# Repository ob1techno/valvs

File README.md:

# Vālvs
A cascading quad tube VCA module in Eurorack format (3U/32hp).

Vālvs provides four gnarly tube VCAs with drive, gain, feedback, and adjustable, switchable distortion controls.

Vālvs’ outputs are daisy-chained, allowing adjacent groups of 2, 3, or all 4 channels to be mixed together.

Based on/inspired by the work of [Ken Stone](https://www.elby-designs.com/webtek/cgs/cgs65/cgs65_vca.html), [L-1](http://l-1.su/TubeVCA.html) and [Émilie Gillet](https://mutable-instruments.net/modules/veils/), using NOS Soviet 1Ж24Б tubes; as used in the Спутник 1 satellite and Восток 1 spacecraft!

## Demos
#### Single channel audio demo

#### Mixer demo

## [Build Guide](https://github.com/ob1techno/valvs/wiki/Vālvs-Build-Guide) 
The [build guide](https://github.com/ob1techno/valvs/wiki/Vālvs-Build-Guide) is available [in the wiki](https://github.com/ob1techno/valvs/wiki/Vālvs-Build-Guide).

## Notes

### Calibration/Adjustment
There are no hard and fast rules here. The module is intended to be pretty flexible in terms of gain/distortion so it's very much a case of setting it up to your own taste. You could calibrate each of the 4 VCAs as closely as possible to each other to keep things consistent or you could set each up to have a different character/flavour. 

Each VCA has 4 trimmers on the back of the PCB:

- Plate; this adjusts the plate resistance between 8.2k and 28.2k, which affects the overall gain of the VCA
- CV Init; this adjusts the initial gain voltage, which can be trimmed to ensure the VCA closes completely
- Clean; adjusts the amount of distortion for the "Clean" mode ("Clean" is a relative term in this case)
- Dist; adjusts the amount of distortion for the "Dirty" mode

It's _fairly_ important to get the CV Init trimmed correctly to avoid any audible bleed, but other than that, it's down to taste. You shoud be aware that with additional gain/distortion, there will be inevitable additional noise, so experiment to find the sweet spots.

### Noise
This is inherently a pretty noisy circuit. The tubes can be a little microphonic (this can be improved a little by mounting with some foam/padding between tube and board). The LEDs in Ken Stone's original design injected some more noise as they were connected to the tube's cathode which is in the signal path. L-1's design removes the LEDs, replacing with a 1/2W resistor to ground. 

I've built the circuit both ways and L-1's design is definitely less noisy. I originally thought I preferred the sound with the LEDs, but with all four VCAs mixed, the noise is too noticable, so I've gone with a resistor to ground! I've kept the LEDs to light the tubes, but these are now powered separately, away from the signal path. Even so, these are still quite noisy VCAs, though I prefer the term characterful!

### KiCad Components

I used some KiCad components/footprints that you might need to install if you want to edit the PCB files. You can find those here:
- [EuroCad](https://github.com/nebs/eurocad)
- [E-Switch](https://www.snapeda.com/parts/100SP1T1B4M2QE/E-Switch/view-part/)

### Parts/Construction
I selected parts for this module based on several factors; what I had in stock already, parts I am familiar with and like to use, availability, etc. This means it may not be the easiest module for some to build. For example, I've used 0603 passives, where I could probably have fit a larger size, or used through-hole components. I made this decision because I have a large stock of 0603 passives and I personally prefer SMT to THT. That said, I don't think this is a difficult build. I've built a few of them and it's a relatively low part count per VCA, so quite quick to put together. The surface mount components used also make this suitable for SMD fabrication/assembly services, which I have used successfully on my latest builds.

The construction should all be self explanatory as it's just a single board. Parts go on the side where their silkscreen is (although if you used particularly tall film box caps, you might need to move them to the back). 

There's also the option of mounting the trimmers for the clean/dirty distortion on the front of the PCB and drilling holes so they're adjustable from the front, if you like that sort of thing. 

It's worth using some heatshrink on the tube legs for peace of mind, though not strictly necessary, and I like to use some acetate sheet to fill the windows in case of dust, stray cables, etc.

[There are some build photos in the wiki.](https://github.com/ob1techno/valvs/wiki/Vālvs-Build-Guide)

### Disclaimer
I am not an electronic engineer. I am a musician/programmer with a keen interest in synthesis and electronics. I am entirely self-taught; this was my first project using KiCad and I'm sure I have made many mistakes. 

I have tried to ensure that this works before publishing my work, but this is presented as-is and with no guarantees or acceptance of responsibility on my part. I'd welcome any feedback and I am interested in improving the design; please use the issues section or submit a pull request. 

I also make no promises to support this project, but do get in touch and I'll help if I can.

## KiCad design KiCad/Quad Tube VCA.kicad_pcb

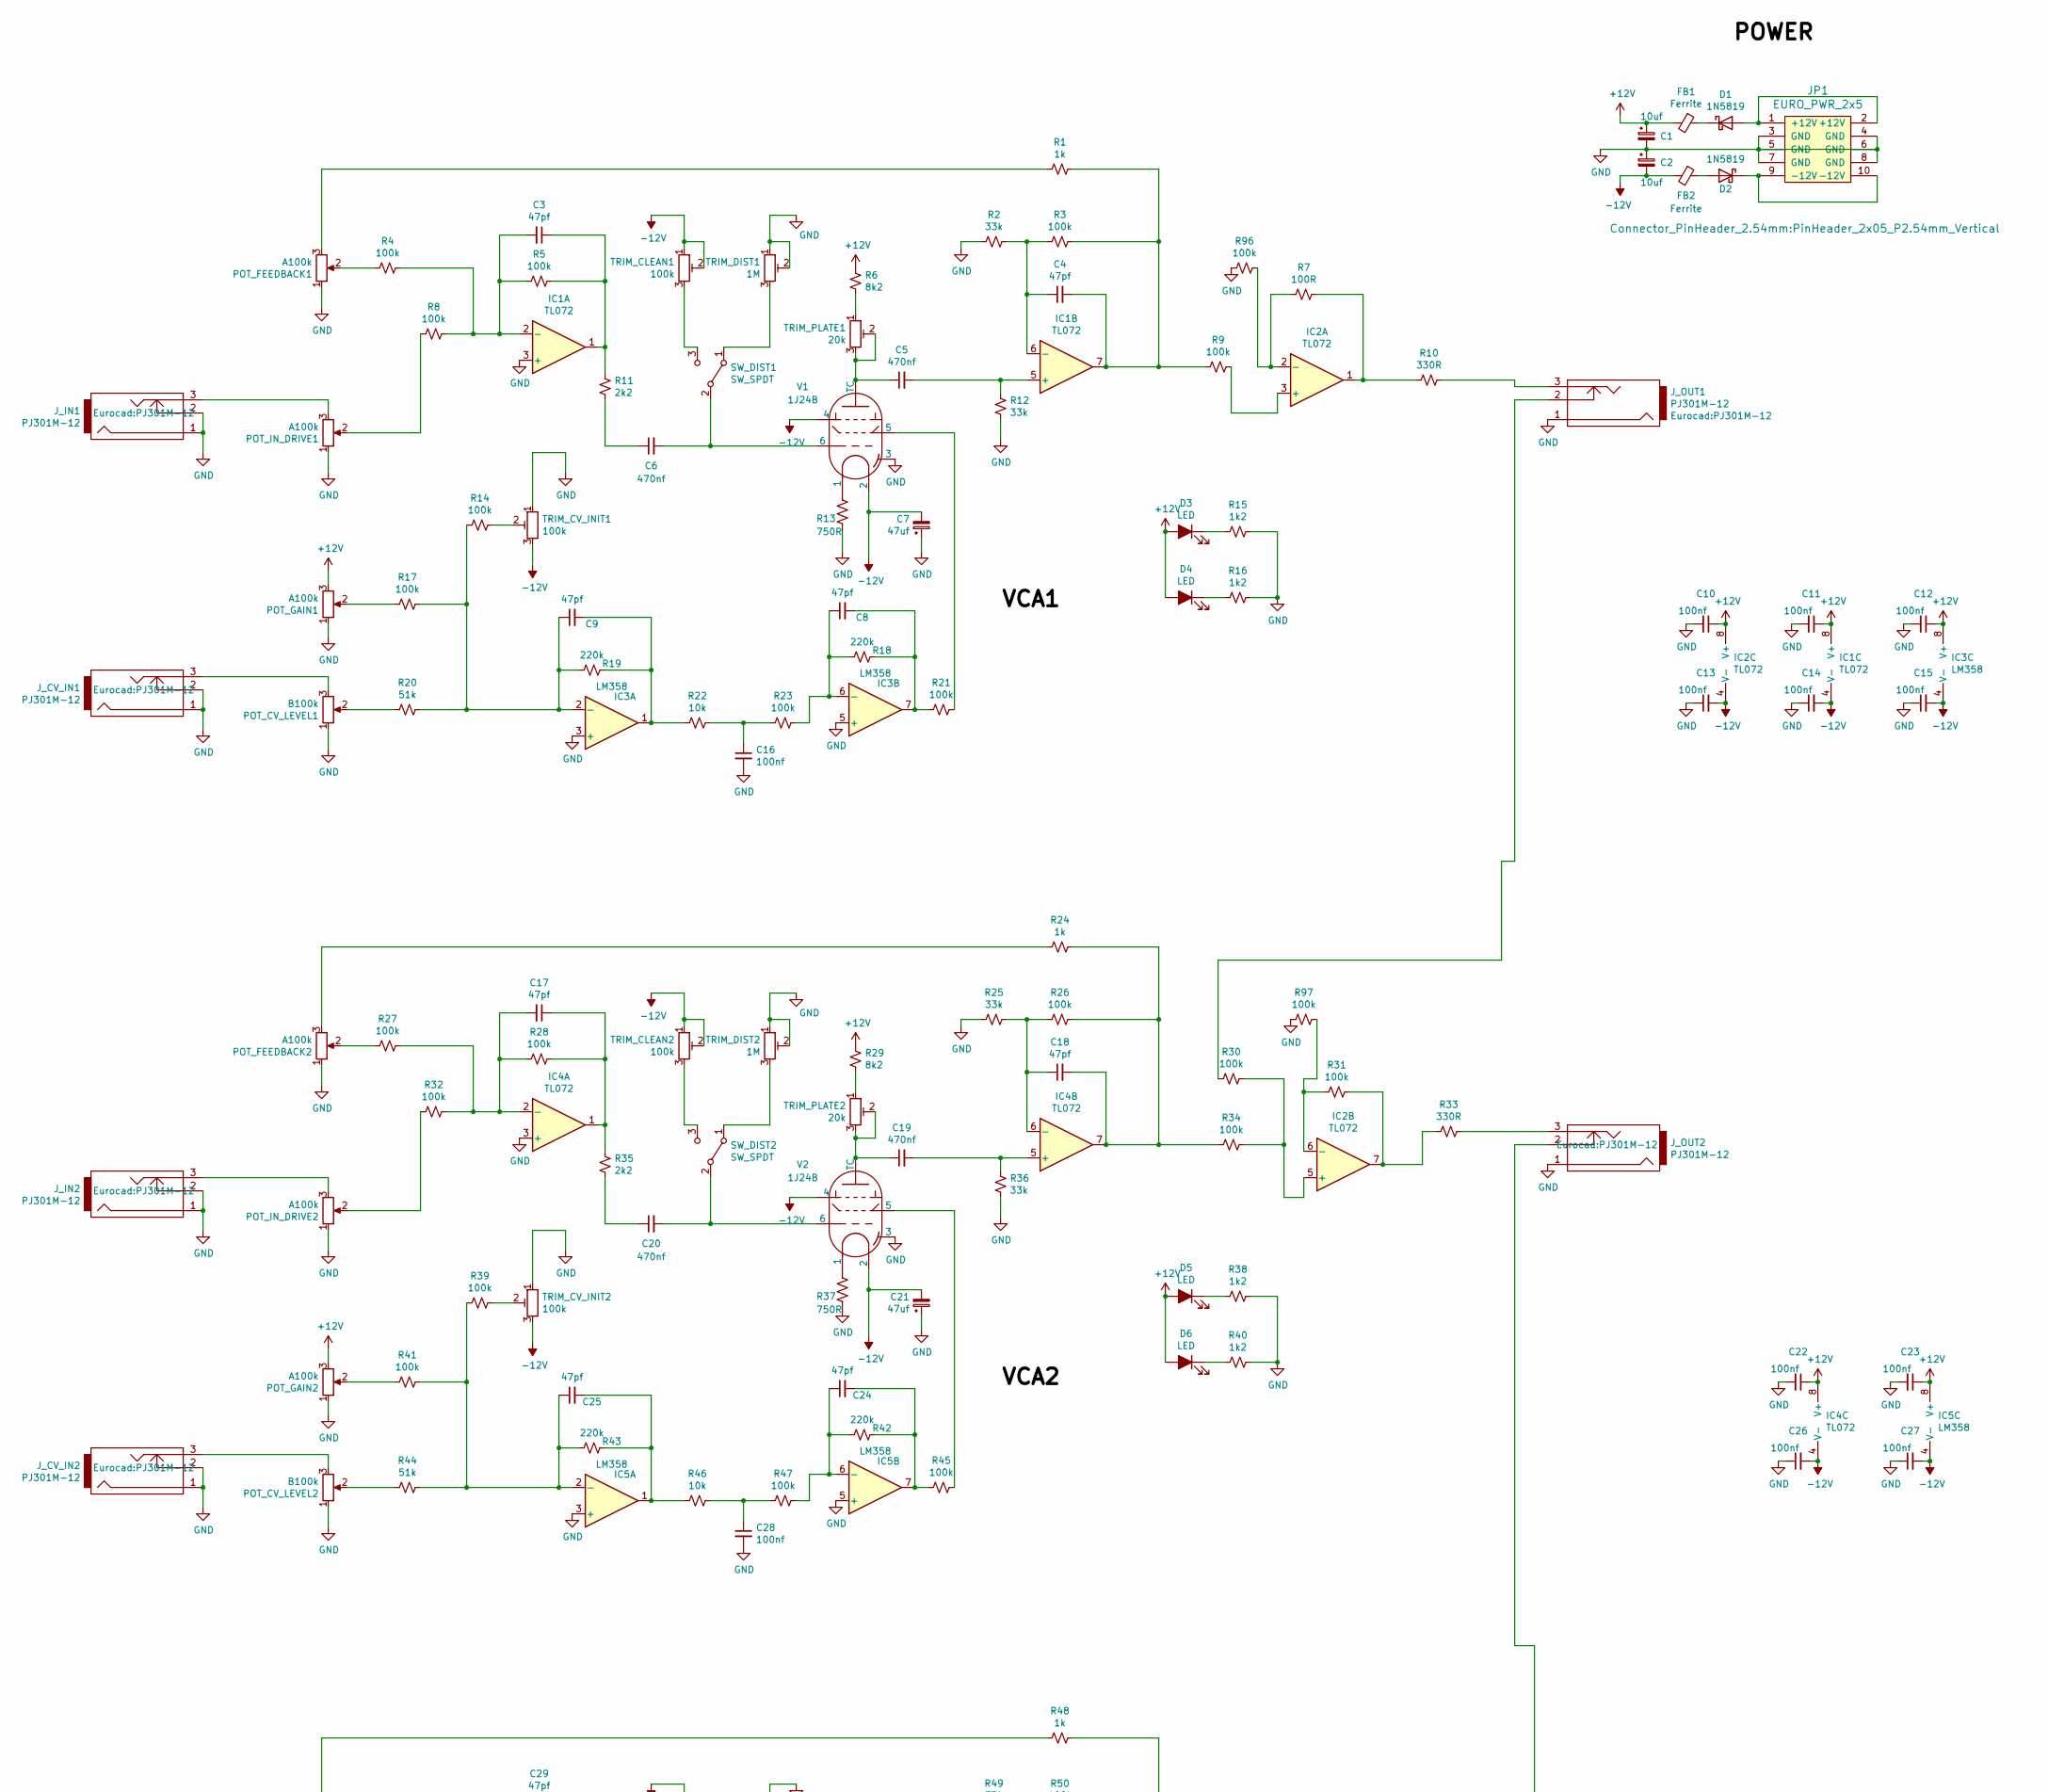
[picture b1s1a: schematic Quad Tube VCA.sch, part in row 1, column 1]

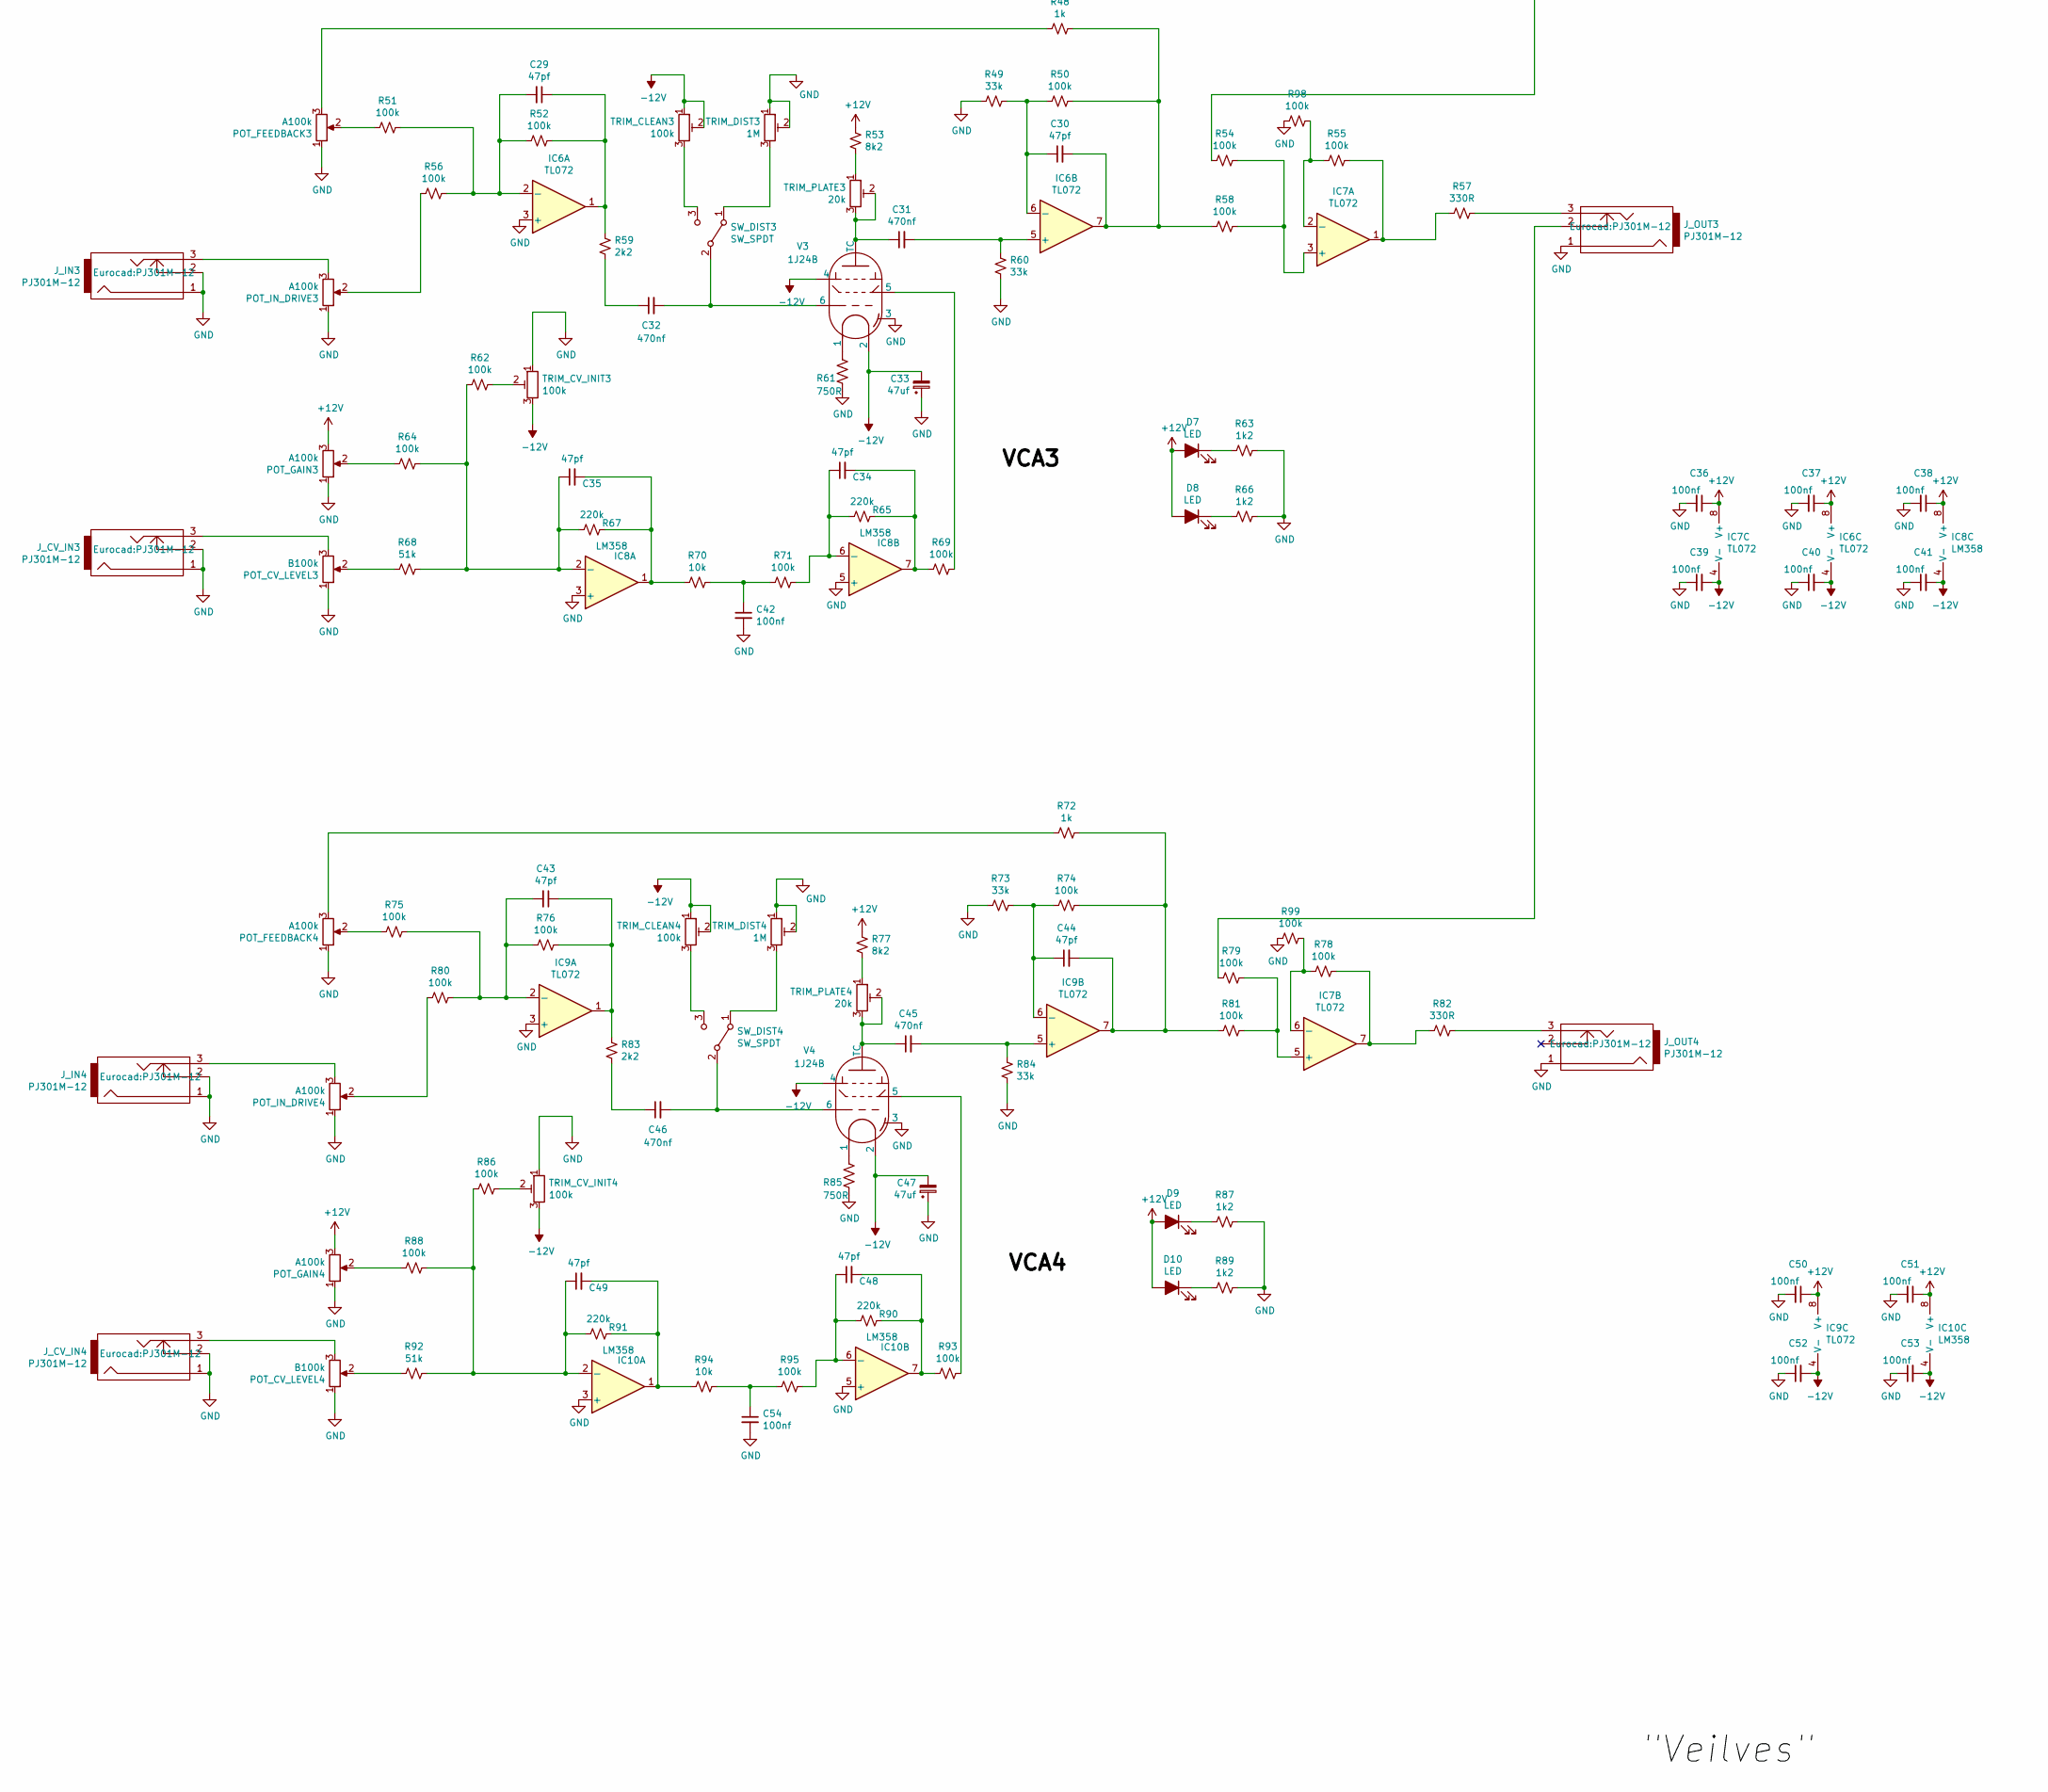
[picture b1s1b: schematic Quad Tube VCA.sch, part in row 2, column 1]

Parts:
C1, C2: 10uf; CP_Radial_D5.0mm_P2.50mm
C3, C4, C8, C9, C17, C18, C24, C25, C29, C30, C34, C35, C43, C44, C48, C49: 47pf; C_0603_1608Metric
C5, C6, C19, C20, C31, C32, C45, C46: 470nf; C_Rect_L7.2mm_W2.5mm_P5.00mm_FKS2_FKP2_MKS2_MKP2
C7, C21, C33, C47: 47uf; CP_Radial_D5.0mm_P2.50mm
C10, C11, C12, C13, C14, C15, C16, C22, C23, C26, C27, C28, C36, C37, C38, C39, C40, C41, C42, C50, C51, C52, C53, C54: 100nf; C_0603_1608Metric
D1, D2: 1N5819; D_SOD-123
D3, D4, D5, D6, D7, D8, D9, D10: LED; LED_D3.0mm
FB1, FB2: Ferrite; R_0603_1608Metric
IC1, IC2, IC4, IC6, IC7, IC9: TL072; SOIC-8_3.9x4.9mm_P1.27mm
IC3, IC5, IC8, IC10: LM358; SOIC-8_3.9x4.9mm_P1.27mm
JP1: EURO_PWR_2x5; PinHeader_2x05_P2.54mm_Vertical
J_CV_IN1, J_CV_IN2, J_CV_IN3, J_CV_IN4: PJ301M-12
J_IN1, J_IN2, J_IN3, J_IN4: PJ301M-12
J_OUT1, J_OUT2, J_OUT3, J_OUT4: PJ301M-12
POT_CV_LEVEL1, POT_CV_LEVEL2, POT_CV_LEVEL3, POT_CV_LEVEL4: B100k; Alpha9mmPot
POT_FEEDBACK1, POT_FEEDBACK2, POT_FEEDBACK3, POT_FEEDBACK4: A100k; Alpha9mmPot
POT_GAIN1, POT_GAIN2, POT_GAIN3, POT_GAIN4: A100k; Alpha9mmPot
POT_IN_DRIVE1, POT_IN_DRIVE2, POT_IN_DRIVE3, POT_IN_DRIVE4: A100k; Alpha9mmPot
R1, R24, R48, R72: 1k; R_0603_1608Metric
R2, R12, R25, R36, R49, R60, R73, R84: 33k; R_0603_1608Metric
R3, R4, R5, R8, R9, R14, R17, R21, R23, R26, R27, R28, R30, R31, R32, R34, R39, R41, R45, R47, R50, R51, R52, R54, R55, R56, R58, R62, R64, R69, R71, R74, R75, R76, R78, R79, R80, R81, R86, R88, R93, R95, R96, R97, R98, R99: 100k; R_0603_1608Metric
R6, R29, R53, R77: 8k2; R_0603_1608Metric
R7: 100R; R_0603_1608Metric
R10, R33, R57, R82: 330R; R_0603_1608Metric
R11, R35, R59, R83: 2k2; R_0603_1608Metric
R13, R37, R61, R85: 750R; R_1210_3225Metric
R15, R16, R38, R40, R63, R66, R87, R89: 1k2; R_0603_1608Metric
R18, R19, R42, R43, R65, R67, R90, R91: 220k; R_0603_1608Metric
R20, R44, R68, R92: 51k; R_0603_1608Metric
R22, R46, R70, R94: 10k; R_0603_1608Metric
SW_DIST1, SW_DIST2, SW_DIST3, SW_DIST4: SW_SPDT; SW_100SP1T1B4M2QE
TRIM_CLEAN1, TRIM_CLEAN2, TRIM_CLEAN3, TRIM_CLEAN4: 100k; Potentiometer_Bourns_3296W_Vertical
TRIM_CV_INIT1, TRIM_CV_INIT2, TRIM_CV_INIT3, TRIM_CV_INIT4: 100k; Potentiometer_Bourns_3296W_Vertical
TRIM_DIST1, TRIM_DIST2, TRIM_DIST3, TRIM_DIST4: 1M; Potentiometer_Bourns_3296W_Vertical
TRIM_PLATE1, TRIM_PLATE2, TRIM_PLATE3, TRIM_PLATE4: 20k; Potentiometer_Bourns_3296W_Vertical
V1, V2, V3, V4: 1J24B; Valve_Mini_Pentode_1j24b

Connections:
+12V: C1.1, C10.1, C11.1, C12.1, C22.1, C23.1, C36.1, C37.1, C38.1, C50.1, C51.1, D3.2 (A), D4.2 (A), D5.2 (A), D6.2 (A), D7.2 (A), D8.2 (A), D9.2 (A), D10.2 (A), FB1.2, IC1.8 (V+), IC2.8 (V+), IC3.8 (V+), IC4.8 (V+), IC5.8 (V+), IC6.8 (V+), IC7.8 (V+), IC8.8 (V+), IC9.8 (V+), IC10.8 (V+), POT_GAIN1.3, POT_GAIN2.3, POT_GAIN3.3, POT_GAIN4.3, R6.1, R29.1, R53.1, R77.1
-12V: C2.2, C7.2, C13.2, C14.2, C15.2, C21.2, C26.2, C27.2, C33.2, C39.2, C40.2, C41.2, C47.2, C52.2, C53.2, FB2.2, IC1.4 (V-), IC2.4 (V-), IC3.4 (V-), IC4.4 (V-), IC5.4 (V-), IC6.4 (V-), IC7.4 (V-), IC8.4 (V-), IC9.4 (V-), IC10.4 (V-), TRIM_CLEAN1.1, TRIM_CLEAN1.2, TRIM_CLEAN2.1, TRIM_CLEAN2.2, TRIM_CLEAN3.1, TRIM_CLEAN3.2, TRIM_CLEAN4.1, TRIM_CLEAN4.2, TRIM_CV_INIT1.3, TRIM_CV_INIT2.3, TRIM_CV_INIT3.3, TRIM_CV_INIT4.3, V1.2, V1.4, V2.2, V2.4, V3.2, V3.4, V4.2, V4.4
GND: C1.2, C2.1, C7.1, C10.2, C11.2, C12.2, C13.1, C14.1, C15.1, C16.2, C21.1, C22.2, C23.2, C26.1, C27.1, C28.2, C33.1, C36.2, C37.2, C38.2, C39.1, C40.1, C41.1, C42.2, C47.1, C50.2, C51.2, C52.1, C53.1, C54.2, IC1.3 (+), IC3.3 (+), IC3.5 (+), IC4.3 (+), IC5.3 (+), IC5.5 (+), IC6.3 (+), IC8.3 (+), IC8.5 (+), IC9.3 (+), IC10.3 (+), IC10.5 (+), JP1.3 (GND), JP1.4 (GND), JP1.5 (GND), JP1.6 (GND), JP1.7 (GND), JP1.8 (GND), J_CV_IN1.1, J_CV_IN1.2, J_CV_IN2.1, J_CV_IN2.2, J_CV_IN3.1, J_CV_IN3.2, J_CV_IN4.1, J_CV_IN4.2, J_IN1.1, J_IN1.2, J_IN2.1, J_IN2.2, J_IN3.1, J_IN3.2, J_IN4.1, J_IN4.2, J_OUT1.1, J_OUT2.1, J_OUT3.1, J_OUT4.1, POT_CV_LEVEL1.1, POT_CV_LEVEL2.1, POT_CV_LEVEL3.1, POT_CV_LEVEL4.1, POT_FEEDBACK1.1, POT_FEEDBACK2.1, POT_FEEDBACK3.1, POT_FEEDBACK4.1, POT_GAIN1.1, POT_GAIN2.1, POT_GAIN3.1, POT_GAIN4.1, POT_IN_DRIVE1.1, POT_IN_DRIVE2.1, POT_IN_DRIVE3.1, POT_IN_DRIVE4.1, R2.1, R12.2, R13.2, R15.1, R16.2, R25.1, R36.2, R37.2, R38.1, R40.2, R49.1, R60.2, R61.2, R63.1, R66.2, R73.1, R84.2, R85.2, R87.1, R89.2, R96.2, R97.2, R98.2, R99.2, TRIM_CV_INIT1.1, TRIM_CV_INIT2.1, TRIM_CV_INIT3.1, TRIM_CV_INIT4.1, TRIM_DIST1.1, TRIM_DIST1.2, TRIM_DIST2.1, TRIM_DIST2.2, TRIM_DIST3.1, TRIM_DIST3.2, TRIM_DIST4.1, TRIM_DIST4.2, V1.3, V2.3, V3.3, V4.3
unnamed: C3.1, IC1.1, R5.2, R11.1
unnamed: C3.2, IC1.2 (-), R4.2, R5.1, R8.2
unnamed: C4.1, IC1.6 (-), R2.2, R3.1
unnamed: C4.2, IC1.7, R1.1, R3.2, R9.2
unnamed: C5.1, TRIM_PLATE1.2, TRIM_PLATE1.3, V1.7 (TC)
unnamed: C5.2, IC1.5 (+), R12.1
unnamed: C6.1, R11.2
unnamed: C6.2, SW_DIST1.2 (B), V1.6
unnamed: C8.1, IC3.6 (-), R18.1, R23.2
unnamed: C8.2, IC3.7, R18.2, R21.1
unnamed: C9.1, IC3.2 (-), R14.1, R17.1, R19.1, R20.2
unnamed: C9.2, IC3.1, R19.2, R22.1
unnamed: C16.1, R22.2, R23.1
unnamed: C17.1, IC4.1, R28.2, R35.1
unnamed: C17.2, IC4.2 (-), R27.2, R28.1, R32.2
unnamed: C18.1, IC4.6 (-), R25.2, R26.1
unnamed: C18.2, IC4.7, R24.1, R26.2, R34.2
unnamed: C19.1, TRIM_PLATE2.2, TRIM_PLATE2.3, V2.7 (TC)
unnamed: C19.2, IC4.5 (+), R36.1
unnamed: C20.1, R35.2
unnamed: C20.2, SW_DIST2.2 (B), V2.6
unnamed: C24.1, IC5.6 (-), R42.1, R47.2
unnamed: C24.2, IC5.7, R42.2, R45.1
unnamed: C25.1, IC5.2 (-), R39.1, R41.1, R43.1, R44.2
unnamed: C25.2, IC5.1, R43.2, R46.1
unnamed: C28.1, R46.2, R47.1
unnamed: C29.1, IC6.1, R52.2, R59.1
unnamed: C29.2, IC6.2 (-), R51.2, R52.1, R56.2
unnamed: C30.1, IC6.6 (-), R49.2, R50.1
unnamed: C30.2, IC6.7, R48.1, R50.2, R58.2
unnamed: C31.1, TRIM_PLATE3.2, TRIM_PLATE3.3, V3.7 (TC)
unnamed: C31.2, IC6.5 (+), R60.1
unnamed: C32.1, R59.2
unnamed: C32.2, SW_DIST3.2 (B), V3.6
unnamed: C34.1, IC8.6 (-), R65.1, R71.2
unnamed: C34.2, IC8.7, R65.2, R69.1
unnamed: C35.1, IC8.2 (-), R62.1, R64.1, R67.1, R68.2
unnamed: C35.2, IC8.1, R67.2, R70.1
unnamed: C42.1, R70.2, R71.1
unnamed: C43.1, IC9.1, R76.2, R83.1
unnamed: C43.2, IC9.2 (-), R75.2, R76.1, R80.2
unnamed: C44.1, IC9.6 (-), R73.2, R74.1
unnamed: C44.2, IC9.7, R72.1, R74.2, R81.2
unnamed: C45.1, TRIM_PLATE4.2, TRIM_PLATE4.3, V4.7 (TC)
unnamed: C45.2, IC9.5 (+), R84.1
unnamed: C46.1, R83.2
unnamed: C46.2, SW_DIST4.2 (B), V4.6
unnamed: C48.1, IC10.6 (-), R90.1, R95.2
unnamed: C48.2, IC10.7, R90.2, R93.1
unnamed: C49.1, IC10.2 (-), R86.1, R88.1, R91.1, R92.2
unnamed: C49.2, IC10.1, R91.2, R94.1
unnamed: C54.1, R94.2, R95.1
unnamed: D1.1 (K), FB1.1
unnamed: D1.2 (A), JP1.1 (+12V), JP1.2 (+12V)
unnamed: D2.1 (K), JP1.9 (-12V), JP1.10 (-12V)
unnamed: D2.2 (A), FB2.1
unnamed: D3.1 (K), R15.2
unnamed: D4.1 (K), R16.1
unnamed: D5.1 (K), R38.2
unnamed: D6.1 (K), R40.1
unnamed: D7.1 (K), R63.2
unnamed: D8.1 (K), R66.1
unnamed: D9.1 (K), R87.2
unnamed: D10.1 (K), R89.1
unnamed: IC2.1, R7.1, R10.1
unnamed: IC2.2 (-), R7.2, R96.1
unnamed: IC2.3 (+), R9.1
unnamed: IC2.5 (+), R30.1, R34.1
unnamed: IC2.6 (-), R31.2, R97.1
unnamed: IC2.7, R31.1, R33.1
unnamed: IC7.1, R55.1, R57.1
unnamed: IC7.2 (-), R55.2, R98.1
unnamed: IC7.3 (+), R54.1, R58.1
unnamed: IC7.5 (+), R79.1, R81.1
unnamed: IC7.6 (-), R78.2, R99.1
unnamed: IC7.7, R78.1, R82.1
unnamed: J_CV_IN1.3, POT_CV_LEVEL1.3
unnamed: J_CV_IN2.3, POT_CV_LEVEL2.3
unnamed: J_CV_IN3.3, POT_CV_LEVEL3.3
unnamed: J_CV_IN4.3, POT_CV_LEVEL4.3
unnamed: J_IN1.3, POT_IN_DRIVE1.3
unnamed: J_IN2.3, POT_IN_DRIVE2.3
unnamed: J_IN3.3, POT_IN_DRIVE3.3
unnamed: J_IN4.3, POT_IN_DRIVE4.3
unnamed: J_OUT1.2, R30.2
unnamed: J_OUT1.3, R10.2
unnamed: J_OUT2.2, R54.2
unnamed: J_OUT2.3, R33.2
unnamed: J_OUT3.2, R79.2
unnamed: J_OUT3.3, R57.2
unnamed: J_OUT4.3, R82.2
unnamed: POT_CV_LEVEL1.2, R20.1
unnamed: POT_CV_LEVEL2.2, R44.1
unnamed: POT_CV_LEVEL3.2, R68.1
unnamed: POT_CV_LEVEL4.2, R92.1
unnamed: POT_FEEDBACK1.2, R4.1
unnamed: POT_FEEDBACK1.3, R1.2
unnamed: POT_FEEDBACK2.2, R27.1
unnamed: POT_FEEDBACK2.3, R24.2
unnamed: POT_FEEDBACK3.2, R51.1
unnamed: POT_FEEDBACK3.3, R48.2
unnamed: POT_FEEDBACK4.2, R75.1
unnamed: POT_FEEDBACK4.3, R72.2
unnamed: POT_GAIN1.2, R17.2
unnamed: POT_GAIN2.2, R41.2
unnamed: POT_GAIN3.2, R64.2
unnamed: POT_GAIN4.2, R88.2
unnamed: POT_IN_DRIVE1.2, R8.1
unnamed: POT_IN_DRIVE2.2, R32.1
unnamed: POT_IN_DRIVE3.2, R56.1
unnamed: POT_IN_DRIVE4.2, R80.1
unnamed: R6.2, TRIM_PLATE1.1
unnamed: R13.1, V1.1
unnamed: R14.2, TRIM_CV_INIT1.2
unnamed: R21.2, V1.5
unnamed: R29.2, TRIM_PLATE2.1
unnamed: R37.1, V2.1
unnamed: R39.2, TRIM_CV_INIT2.2
unnamed: R45.2, V2.5
unnamed: R53.2, TRIM_PLATE3.1
unnamed: R61.1, V3.1
unnamed: R62.2, TRIM_CV_INIT3.2
unnamed: R69.2, V3.5
unnamed: R77.2, TRIM_PLATE4.1
unnamed: R85.1, V4.1
unnamed: R86.2, TRIM_CV_INIT4.2
unnamed: R93.2, V4.5
unnamed: SW_DIST1.1 (A), TRIM_DIST1.3
unnamed: SW_DIST1.3 (C), TRIM_CLEAN1.3
unnamed: SW_DIST2.1 (A), TRIM_DIST2.3
unnamed: SW_DIST2.3 (C), TRIM_CLEAN2.3
unnamed: SW_DIST3.1 (A), TRIM_DIST3.3
unnamed: SW_DIST3.3 (C), TRIM_CLEAN3.3
unnamed: SW_DIST4.1 (A), TRIM_DIST4.3
unnamed: SW_DIST4.3 (C), TRIM_CLEAN4.3

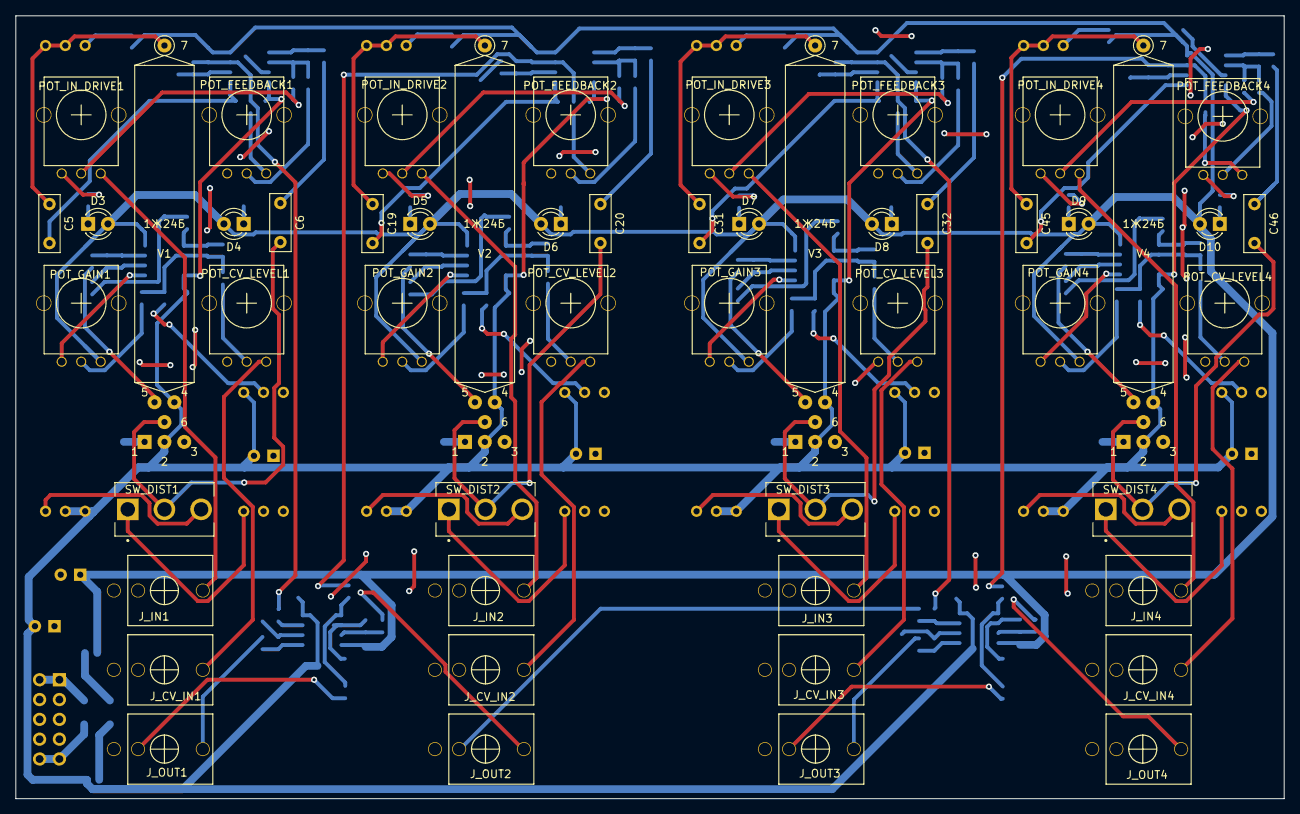
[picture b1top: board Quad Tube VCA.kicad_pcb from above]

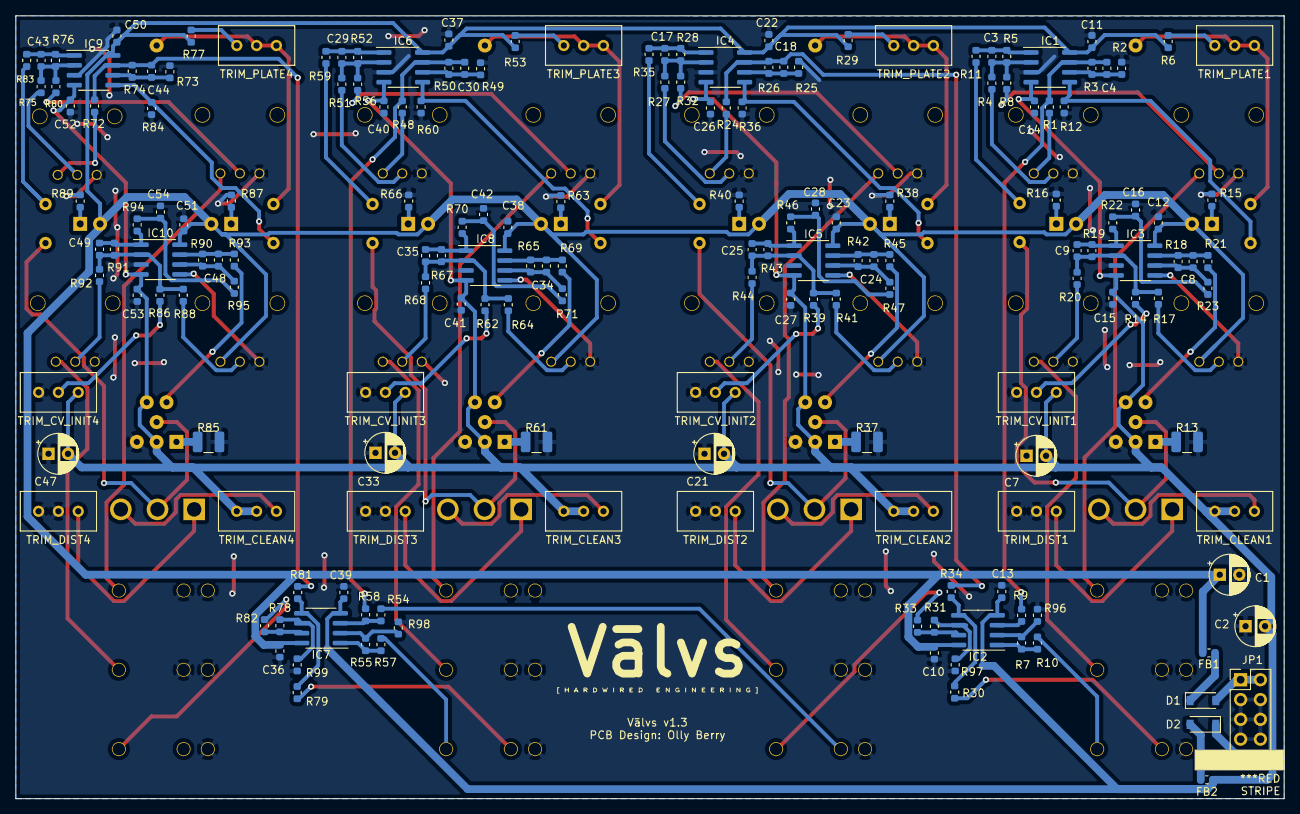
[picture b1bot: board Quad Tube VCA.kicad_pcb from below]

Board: 2 copper layers, 162.6 x 100.3 mm, 228 parts (176 on the bottom side), 138 nets.

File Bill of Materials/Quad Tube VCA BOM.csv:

Comment,Designator,Footprint,LCSC
"10uf","C1,C2","Capacitor_THT:CP_Radial_D5.0mm_P2.50mm",""
"100nf","C10,C11,C12,C13,C14,C15,C16,C22,C23,C26,C27,C28,C36,C37,C38,C39,C40,C41,C42,C50,C51,C52,C53,C54,C55,C56,C57,C58","Capacitor_SMD:C_0603_1608Metric",""
"470nf","C5,C6,C19,C20,C31,C32,C45,C46","Capacitor_THT:C_Rect_L7.2mm_W2.5mm_P5.00mm_FKS2_FKP2_MKS2_MKP2",""
"47uf","C7,C21,C33,C47","Capacitor_THT:CP_Radial_D5.0mm_P2.50mm",""
"47pf","C3,C4,C8,C9,C17,C18,C24,C25,C29,C30,C34,C35,C43,C44,C48,C49","Capacitor_SMD:C_0603_1608Metric",""
"1N5819","D1,D2","Diode_SMD:D_SOD-123",""
"LED","D3,D4,D5,D6,D7,D8,D9,D10","LED_THT:LED_D3.0mm",""
"Ferrite","FB1,FB2","Resistor_SMD:R_0603_1608Metric",""
"LM358","IC3,IC5,IC8,IC10","Package_SO:SOIC-8_3.9x4.9mm_P1.27mm",""
"TL072","IC1,IC2,IC4,IC6,IC7,IC9,IC11,IC12","Package_SO:SOIC-8_3.9x4.9mm_P1.27mm",""
"EURO_PWR_2x5","JP1","Connector_PinHeader_2.54mm:PinHeader_2x05_P2.54mm_Vertical",""
"PJ301M-12","J_OUT1,J_CV_IN1,J_IN1,J_IN2,J_CV_IN2,J_OUT2,J_OUT3,J_CV_IN3,J_IN3,J_CV_IN4,J_IN4,J_OUT4","Eurocad:PJ301M-12",""
"B100k","POT_CV_LEVEL1,POT_CV_LEVEL2,POT_CV_LEVEL3,POT_CV_LEVEL4","Eurocad:Alpha9mmPot",""
"A100k","POT_GAIN1,POT_IN_DRIVE1,POT_FEEDBACK1,POT_FEEDBACK2,POT_IN_DRIVE2,POT_GAIN2,POT_GAIN3,POT_IN_DRIVE3,POT_FEEDBACK3,POT_GAIN4,POT_IN_DRIVE4,POT_FEEDBACK4","Eurocad:Alpha9mmPot",""
"1k","R1,R24,R48,R72","Resistor_SMD:R_0603_1608Metric",""
"330R","R10,R33,R57,R82","Resistor_SMD:R_0603_1608Metric",""
"2k2","R11,R35,R59,R83","Resistor_SMD:R_0603_1608Metric",""
"33k","R12,R36,R60,R84","Resistor_SMD:R_0603_1608Metric",""
"220k","R18,R19,R42,R43,R65,R67,R90,R91","Resistor_SMD:R_0603_1608Metric",""
"51k","R20,R44,R68,R92","Resistor_SMD:R_0603_1608Metric",""
"100k","R2,R3,R4,R5,R7,R8,R9,R14,R17,R21,R23,R25,R26,R27,R28,R30,R31,R32,R34,R39,R41,R45,R47,R49,R50,R51,R52,R54,R55,R56,R58,R62,R64,R69,R71,R73,R74,R75,R76,R78,R79,R80,R81,R86,R88,R93,R95,R96,R97,R98,R99,R100,R101","Resistor_SMD:R_0603_1608Metric",""
"10k","R22,R46,R70,R94","Resistor_SMD:R_0603_1608Metric",""
"1k2","R15,R16,R38,R40,R63,R66,R87,R89","Resistor_SMD:R_0603_1608Metric",""
"8k2","R6,R29,R53,R77","Resistor_SMD:R_0603_1608Metric",""
"750R","R13,R37,R61,R85","Resistor_SMD:R_1206_3216Metric",""
"SW_SPDT","SW_DIST1,SW_DIST2,SW_DIST3,SW_DIST4","100SP1T1B4M2QE:SW_100SP1T1B4M2QE",""
"100k","TRIM_CV_INIT1,TRIM_CLEAN1,TRIM_CLEAN2,TRIM_CV_INIT2,TRIM_CV_INIT3,TRIM_CLEAN3,TRIM_CV_INIT4,TRIM_CLEAN4","Potentiometer_THT:Potentiometer_Bourns_3296W_Vertical",""
"1M","TRIM_DIST1,TRIM_DIST2,TRIM_DIST3,TRIM_DIST4","Potentiometer_THT:Potentiometer_Bourns_3296W_Vertical",""
"20k","TRIM_PLATE1,TRIM_PLATE2,TRIM_PLATE3,TRIM_PLATE4","Potentiometer_THT:Potentiometer_Bourns_3296W_Vertical",""
"1J24B","V1,V2,V3,V4","Valve:Valve_Mini_Pentode_1j24b",""

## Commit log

2021-12-31 initial v0.1 commit
2022-01-01 power and vca1 routed
2022-01-01 changes footprints for pots/jacks
2022-01-01 upadtes 3d models, makes more space at pcb edges
2022-01-01 updates layout
2022-01-01 starts work on power traces
2022-01-01 routes power traces
2022-01-01 routes nets for vca4 op amps
2022-01-01 routes nets for remaining op amps
2022-01-01 fixes ground nets
2022-01-01 hooks up all nets
2022-01-01 fixes gnd in op amp section
2022-01-01 fixes gnd everywhere
2022-01-01 avoids jack centers
2022-01-01 updates silkscreen
2022-01-02 adds v0.3 gerbers
2022-01-02 adds v0.3 panel
2022-01-02 adds FreeCAD model
2022-01-02 fixes pot placement issue
2022-01-02 updates project structure
2022-01-03 tightens up panel design
2022-01-03 updates panel image
2022-01-03 crops panel image
2022-01-03 renames panel image
2022-01-15 adds v0.5 gerbers
2022-01-16 adds summing mixers to outputs
2022-01-16 adds mixer parts to pcb - needs re-routing
2022-01-16 cleans up refs
2022-01-16 updates footprints/models
2022-01-16 updates positions
2022-01-16 tightens up positions
2022-01-16 updates footprints in schematic
2022-01-16 syncs pcb/schem
2022-01-16 first GND pour
2022-01-16 +12V net
2022-01-16 -12V net
2022-01-16 connects easy nets
2022-01-16 connects some trickier nets
2022-01-17 tightens gnd pour clearance
2022-01-17 everything connected
2022-01-17 syncs with pcb
2022-01-17 updates panel
2022-01-18 tightens panel positions
2022-01-18 adds copper to panel
2022-01-18 text positions
2022-01-18 adds v0.6 gerbers
2022-01-18 tweaks panel pcb layers
2022-01-19 adds copper to front of panel
2022-01-19 updates v0.6 gerbers
2022-01-19 updates images
2022-01-20 updates panel copper/silkscreen
2022-01-20 updates panel copper/silkscreen again
2022-01-22 flips pots on schematic
2022-01-22 reroutes pots on PCB
2022-01-24 adds new images
2022-01-24 updates PCB silkscreen
2022-01-24 adds keepouts for jack tips
2022-01-24 lays some long traces
2022-01-24 connects -12V
2022-01-24 connects +12V
2022-01-24 op amp traces [WIP]
2022-01-24 updates panel fonts
2022-01-24 all connected
2022-01-24 updates gerbers
2022-01-24 removes unnecessary files
2022-01-25 adds BOM
2022-01-25 updates dir structure
2022-01-25 updates panel drawings
2022-01-25 adds image
2022-01-26 adds reverse power protection diodes
2022-01-26 removes leds from cathode/signal path
2022-01-27 updates annotations - need to regen BOM
2022-01-27 updates GND
2022-01-27 updates BOM
2022-01-28 removes leds from signal path
2022-02-08 updates readme/images
2022-02-08 enlarges panel holes for switches
2022-02-08 removes outdated BOM
2022-02-08 archives v0.7 BOM
2022-02-08 updates readme
2022-02-11 updates v0.7 BOM
2022-02-22 adds v1.01 images
2022-02-23 fix: #3 updates ref. on bom
2022-02-23 adds stealth mode image
2022-03-04 adds inverting buffers, new layout
2022-03-04 routes new layout
2022-03-04 fix: #4 adds new gerbers
2022-03-04 updates BOMs
2022-03-04 adds new BOM/pos
2022-03-04 removes old gerbers
2022-03-04 updates image
2022-03-04 1.2 pcb update
2022-03-15 1.3 pcb update
2022-03-15 updates feedback resistor value for vca1
2022-03-25 v1.3 release
2022-03-26 adds user manual
2022-03-26 updates manual
